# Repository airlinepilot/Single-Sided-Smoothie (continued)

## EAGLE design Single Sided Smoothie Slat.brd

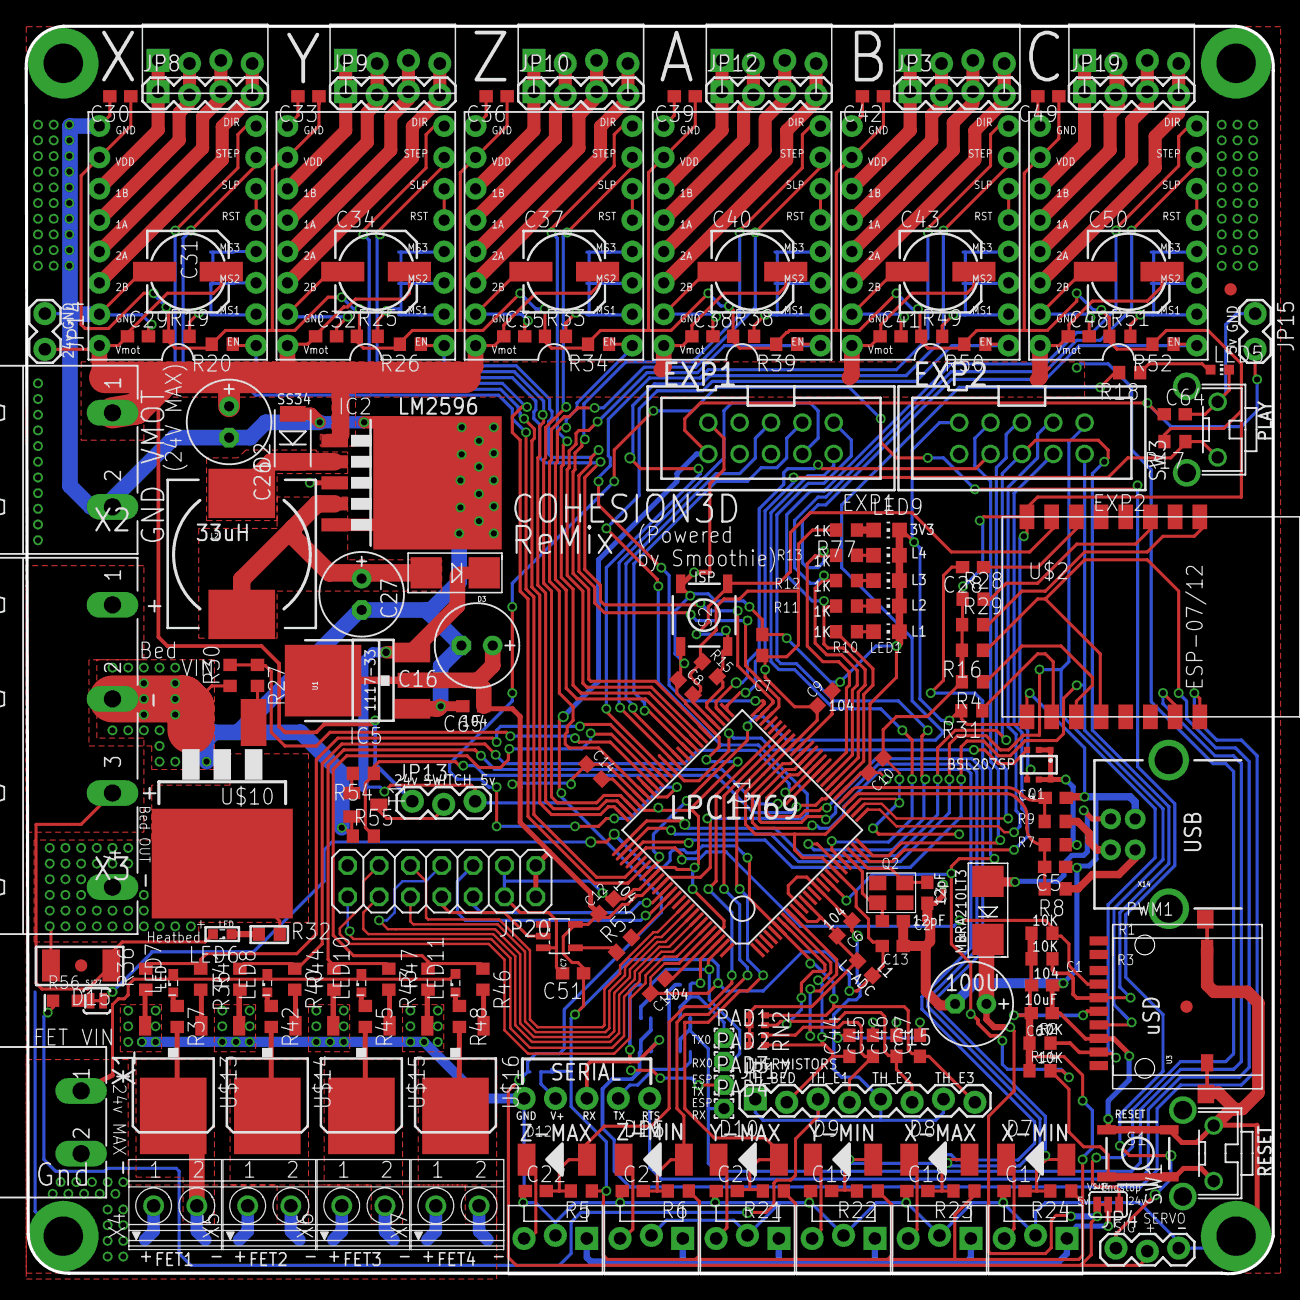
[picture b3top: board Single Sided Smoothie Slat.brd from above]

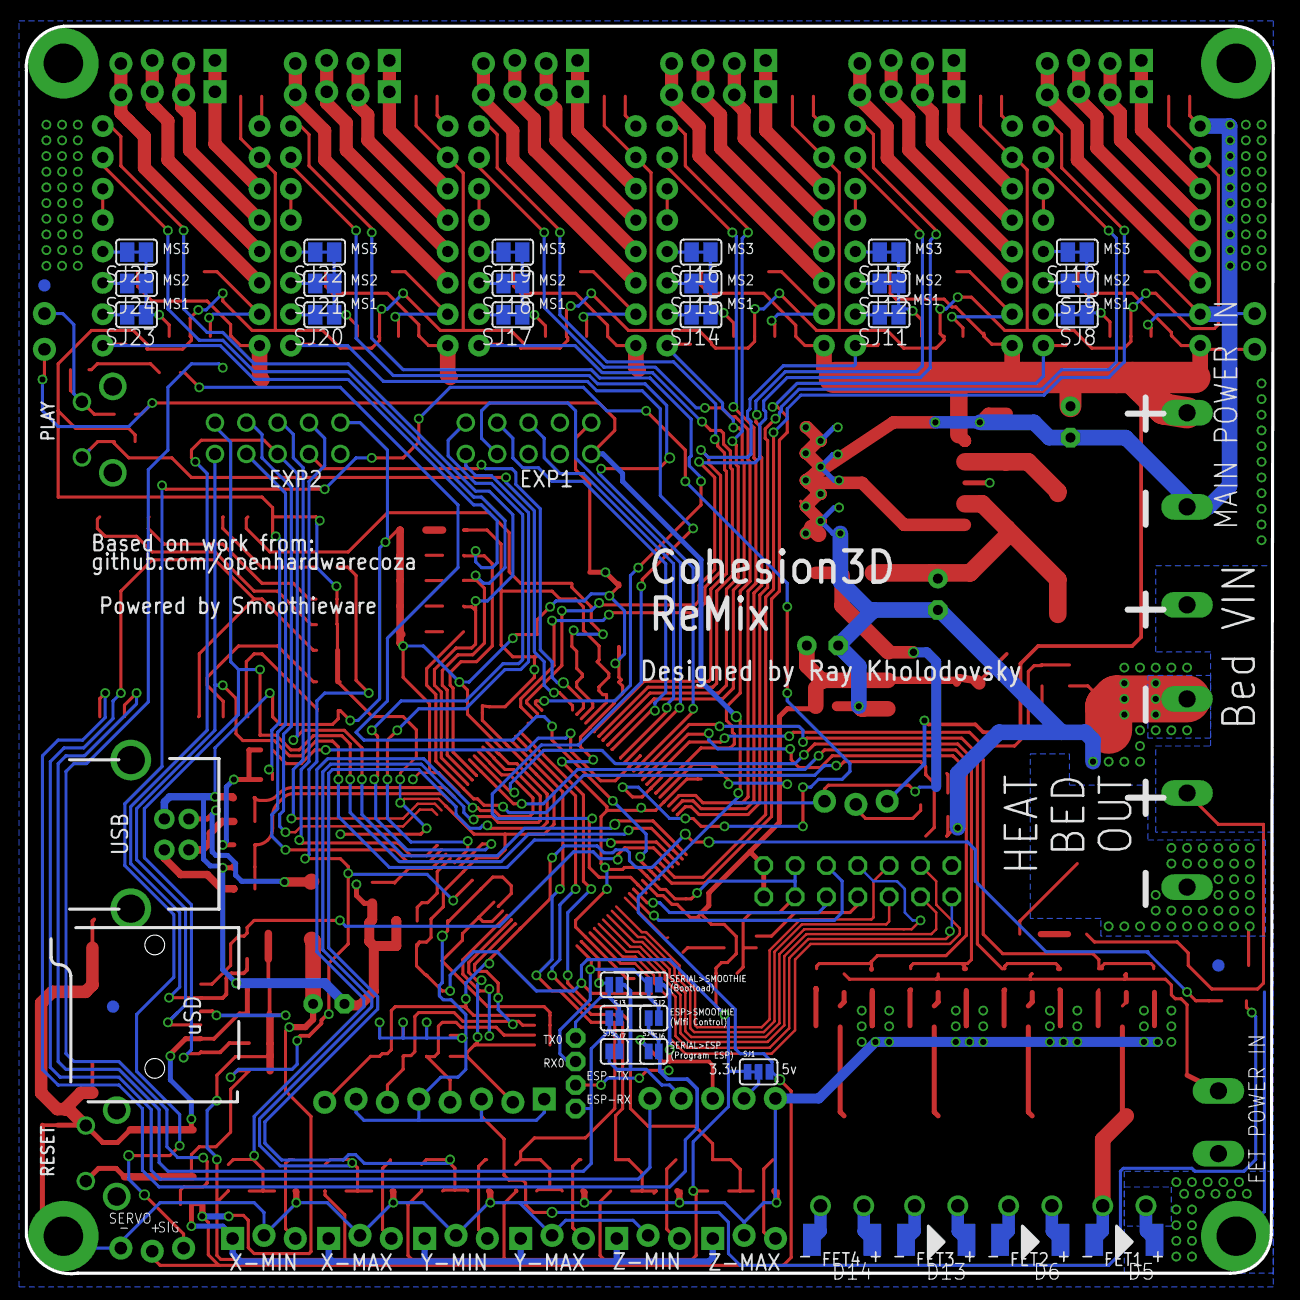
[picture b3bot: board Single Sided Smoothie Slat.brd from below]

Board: 2 copper layers, 101.0 x 101.0 mm, 233 parts (32 on the bottom side), 179 nets.

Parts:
C1, C6, C11, C12, C51, C65: .1uF; C0603
C2, C3: 12pF; C0603
C4, C5: 18pF; C0603
C7, C44, C45, C46, C47, C64, C67: 10uF; C0603
C8, C9, C10, C13, C14, C17, C18, C19, C20, C21, C22, C28, C29, C30, C32, C33, C35, C36, C38, C39, C41, C42, C48, C49: 104; C0603
C15: E2,5-7
C16: 100U; E2,5-7
C26, C27: 220u; E2,5-7
C31, C34, C37, C40, C43, C50: 100uF; 153CLV-0605
D1, D3: MBRA210LT3; SMADIODE
D2: DO-214AC
D5, D6, D7, D8, D9, D10, D11, D12, D13, D14, D15: M4; SOD87
EXP1, EXP2: 2510-; PAK100/2500-10
IC1: LPC1769; LQFP100
IC2: TO263-5
IC5: LD117ADT33TR; DPACK
IC7: 74LVC1G04; SOT23-5
JP1, JP2, JP6, JP7, JP11, JP18: MOLEX-1X4_LOCK
JP3, JP8, JP9, JP10, JP12, JP19: 1X04_LOCK
JP4, JP13: 1X03_LOCK
JP5: 1X05_NO_SILK
JP14, JP15: 1X02_LOCK
JP17: 1X08_LOCK
JP20: 2X07
L1: 0603
L2: 33uH; CDRH125
LED1, LED2, LED3, LED4, LED9: CHIP-LED0805
LED5: CHIP-LED0603
LED6, LED7: SML0603
LED8, LED10, LED11: LED; SML0603
PAD1, PAD2, PAD3, PAD4: 1,6/0,9
Q1: BSL207SP; SC74_INFINEON
Q2: 12MHz; CRYSTAL_3.2X2.5
R1, R2, R3, R4, R14, R15, R16, R17, R28, R29, R31: 10K; R0603
R5, R6, R20, R21, R22, R23, R24, R26, R34, R39, R50, R52: 10k; R0603
R7: 1.5K; R0603
R8, R9: 33R; R0603
R10, R11, R12, R13, R77: R0603
R18, R19, R25, R33, R38, R49, R51: 1k; R0603
R27, R35, R40, R43, R46, R54: 10r; R0603
R30, R36, R41, R44, R47, R55: 100k; R0603
R32, R37, R42, R45, R48: 1.5k; R0603
R53: 22R; R0603
R56: THERM; CT/CN0603
RN2: 4k7; 0603-ARV
S1, S2: TACTILE_SWITCH_SMD
SJ1, SJ26: SJ_3
SJ2, SJ3, SJ4, SJ5, SJ6, SJ7: SJ_2S
SJ8, SJ9, SJ10, SJ11, SJ12, SJ13, SJ14, SJ15, SJ16, SJ17, SJ18, SJ19, SJ20, SJ21, SJ22, SJ23, SJ24, SJ25: SJ
SJ27: THERM-JUMPER; SJ_2S-TRACE
SW1, SW3: SW_TACT_4P_B; SW_TACT_STANDARD_RIGHT_ANGLE
T1: BC817; SOT23-BEC
U1: SOT223
U3: USD-SOCKETUSD; USD-SOCKET-PP
U$1, U$5, U$6, U$7, U$8, U$9: POLOLU_A4983CARRIER; A4988BREAKOUT
U$2: ESP8266_ESP-12; ESP8266-ESP12
U$10: SUM120N04-1M7L-GE3; D2PACK
U$11, U$12, U$17, U$18, U$19, U$20: FIDUCIAL; FIDUCIAL_1MM
U$13, U$14, U$15, U$16: IRLR024; D-PAK_TO252AA
X1: MSTBA2
X2: GMSTBA2
X3: GMSTBA4
X4, X5, X6, X7: 1751248
X14: USBPTH; USB-B-PTH
XMN: MOLEX-1X3_LOCK
XMX: MOLEX-1X3_LOCK
YMN: MOLEX-1X3_LOCK
YMX: MOLEX-1X3_LOCK
ZMN: MOLEX-1X3_LOCK
ZMX: MOLEX-1X3_LOCK

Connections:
1A1M: JP6.2, JP8.2, U$1.1A
1A2M: JP2.2, JP9.2, U$5.1A
1A3M: JP7.2, JP10.2, U$6.1A
1A$4M: JP11.2, JP12.2, U$7.1A
1A$5M: JP1.2, JP3.2, U$8.1A
1A$6M: JP18.2, JP19.2, U$9.1A
1B1M: JP6.1, JP8.1, U$1.1B
1B2M: JP2.1, JP9.1, U$5.1B
1B3M: JP7.1, JP10.1, U$6.1B
1B$4M: JP11.1, JP12.1, U$7.1B
1B$5M: JP1.1, JP3.1, U$8.1B
1B$6M: JP18.1, JP19.1, U$9.1B
2: R4.1, U$2.3
2A1M: JP6.3, JP8.3, U$1.2A
2A2M: JP2.3, JP9.3, U$5.2A
2A3M: JP7.3, JP10.3, U$6.2A
2A$4M: JP11.3, JP12.3, U$7.2A
2A$5M: JP1.3, JP3.3, U$8.2A
2A$6M: JP18.3, JP19.3, U$9.2A
2B1M: JP6.4, JP8.4, U$1.2B
2B2M: JP2.4, JP9.4, U$5.2B
2B3M: JP7.4, JP10.4, U$6.2B
2B$4M: JP11.4, JP12.4, U$7.2B
2B$5M: JP1.4, JP3.4, U$8.2B
2B$6M: JP18.4, JP19.4, U$9.2B
3.3V: C1.2, C7.1, C8.2, C9.2, C10.2, C11.2, C12.2, C13.2, C14.2, C16.+, C30.1, C33.1, C36.1, C39.1, C42.1, C49.1, C51.1, C65.1, C67.2, IC1.19, IC1.28, IC1.42, IC1.54, IC1.71, IC1.84, IC1.96, IC5.4, IC7.5, JP5.4, JP20.1, JP20.2, L1.2, Q1.4, R1.2, R2.2, R3.2, R4.2, R5.1, R6.1, R14.2, R15.2, R16.2, R17.2, R19.1, R20.2, R21.1, R22.1, R23.1, R24.1, R25.1, R26.2, R28.1, R29.1, R33.1, R34.2, R38.1, R39.2, R49.1, R50.2, R51.1, R52.2, R77.2, SJ1.1, SJ1.2, U1.2, U1.4, U3.4, U$1.VDD, U$2.16, U$5.VDD, U$6.VDD, U$7.VDD, U$8.VDD, U$9.VDD
5V: C15.+, C64.1, D1.C, D3.C, EXP1.10, IC5.3, JP4.2, JP13.3, JP15.2, SJ1.3, SJ26.1, U1.3
5VREG: C27.+, D3.A, IC2.4, L2.2
12: C28.1, U$2.14
15: R31.1, U$2.2
24V: C26.+, C29.1, C31.+, C32.1, C34.+, C35.1, C37.+, C38.1, C40.+, C41.1, C43.+, C48.1, C50.+, IC2.1, JP13.1, JP14.2, SJ26.3, U$1.VMOT, U$5.VMOT, U$6.VMOT, U$7.VMOT, U$8.VMOT, U$9.VMOT, X2.1
AGND: C6.2, C44.2, C45.2, C46.2, C47.2, IC1.11, IC1.15, JP17.1, JP17.3, JP17.5, JP17.7, R56.1
AVCC: C6.1, IC1.10, IC1.12, L1.1, RN2.5, RN2.6, RN2.7, RN2.8
BUZZER-RRD: EXP1.1, IC1.20
DIR1: IC1.80, U$1.DIR
DIR2: IC1.49, U$5.DIR
DIR3: IC1.58, U$6.DIR
DIR4: IC1.56, U$7.DIR
DIR5: IC1.50, U$8.DIR
E1-CONTROL: D5.2, R37.2, U$13.4, X4.2
E2-CONTROL: D6.2, R42.2, U$14.4, X5.2
E3-CONTROL: D13.2, R45.2, U$15.4, X6.2
E4-CONTROL: D14.2, R48.2, U$16.4, X7.2
EN1: IC1.81, R20.1, U$1.EN
EN2: IC1.48, R26.1, U$5.EN
EN3: IC1.59, R34.1, U$6.EN
EN4: IC1.57, R39.1, U$7.EN
EN5: IC1.85, R50.1, U$8.EN
ENET_CRS: IC1.92, JP20.7
ENET_MDC: IC1.87, JP20.5
ENET_MDIO: IC1.86, JP20.6
ENET_REF_CLK: IC1.88, R53.2
ENET_RXD0: IC1.91, JP20.10
ENET_RXD1: IC1.90, JP20.9
ENET_TXD0: IC1.95, JP20.11
ENET_TXD1: IC1.94, JP20.14
ENET_TX_EN: IC1.93, JP20.12
ESPRX: PAD4.1, SJ5.2, SJ7.2, U$2.7
ESPTX: PAD3.1, SJ4.2, SJ6.2, U$2.8
GND: C1.1, C2.2, C3.2, C4.1, C5.1, C7.2, C8.1, C9.1, C10.1, C11.1, C12.1, C13.1, C14.1, C15.-, C16.-, C17.1, C18.1, C19.1, C20.1, C21.1, C22.1, C26.-, C27.-, C29.2, C30.2, C31.-, C32.2, C33.2, C34.-, C35.2, C36.2, C37.-, C38.2, C39.2, C40.-, C41.2, C42.2, C43.-, C48.2, C49.2, C50.-, C51.2, C64.2, C65.2, C67.1, D2.2, EXP1.9, EXP2.9, IC1.31, IC1.41, IC1.55, IC1.72, IC1.83, IC1.97, IC2.3, IC2.5, IC2.6, IC5.1, IC7.3, JP4.3, JP5.5, JP14.1, JP15.1, JP20.3, JP20.4, LED1.C, LED2.C, LED3.C, LED4.C, LED5.C, LED9.C, R30.1, R31.2, R36.1, R41.1, R44.1, R47.1, R55.1, S1.3, S1.4, S2.3, S2.4, SW1.2, SW3.2, T1.E, U1.1, U3.6, U3.CDNC1, U3.CDNC2, U3.GND1, U3.GND2, U$1.GND, U$1.GND@0, U$2.1, U$5.GND, U$5.GND@0, U$6.GND, U$6.GND@0, U$7.GND, U$7.GND@0, U$8.GND, U$8.GND@0, U$9.GND, U$9.GND@0, U$10.3, U$13.3, U$14.3, U$15.3, U$16.3, X1.2, X2.2, X3.2, X14.GND, XMN.2, XMX.2, YMN.2, YMX.2, ZMN.2, ZMX.2
HEATBED-CONTROL: D15.2, R32.2, U$10.2, X3.4
HEATBEDVIN: D15.1, LED6.A, X3.1, X3.3
HEATERVIN: D5.1, D6.1, D13.1, D14.1, LED7.A, LED8.A, LED10.A, LED11.A, X1.1, X4.1, X5.1, X6.1, X7.1
ISP_BOOT: IC1.53, R15.1, S2.1, S2.2, U$2.15
LED1: IC1.32, R10.2, R54.1, R55.2
LED2: IC1.33, R11.2, U$9.DIR
LED3: IC1.34, R12.2, U$9.STEP
LED4: IC1.35, R13.2, R52.1, U$9.EN
MOSI1: EXP1.3, IC1.60
unnamed: C2.1, IC1.22, Q2.2
unnamed: C3.1, IC1.23, Q2.1
unnamed: LED5.A, R18.1
unnamed: D11.1, ZMN.3
unnamed: D10.1, YMX.3
unnamed: SJ8.2, U$1.MS1
unnamed: D9.1, YMN.3
unnamed: SJ9.2, U$1.MS2
unnamed: D2.1, IC2.2, L2.1
unnamed: SJ10.2, U$1.MS3
unnamed: D8.1, XMX.3
unnamed: U$5.RST, U$5.SLP
unnamed: D7.1, XMN.3
unnamed: R25.2, SJ11.1, SJ12.1, SJ13.1
unnamed: SJ11.2, U$5.MS1
unnamed: D12.1, ZMX.3
unnamed: SJ12.2, U$5.MS2
unnamed: R28.2, U$2.11
unnamed: SJ13.2, U$5.MS3
unnamed: R27.2, U$10.1
unnamed: LED6.C, R32.1
unnamed: U$6.RST, U$6.SLP
unnamed: R33.2, SJ14.1, SJ15.1, SJ16.1
unnamed: SJ14.2, U$6.MS1
unnamed: SJ15.2, U$6.MS2
unnamed: SJ16.2, U$6.MS3
unnamed: R35.2, U$13.1
unnamed: R19.2, SJ8.1, SJ9.1, SJ10.1
unnamed: LED7.C, R37.1
unnamed: U$7.RST, U$7.SLP
unnamed: R38.2, SJ17.1, SJ18.1, SJ19.1
unnamed: SJ17.2, U$7.MS1
unnamed: SJ18.2, U$7.MS2
unnamed: U$1.RST, U$1.SLP
unnamed: SJ19.2, U$7.MS3
unnamed: R40.2, U$14.1
unnamed: LED8.C, R42.1
unnamed: R43.2, U$15.1
unnamed: LED10.C, R45.1
unnamed: R46.2, U$16.1
unnamed: LED11.C, R48.1
unnamed: U$8.RST, U$8.SLP
unnamed: R49.2, SJ20.1, SJ21.1, SJ22.1
unnamed: SJ20.2, U$8.MS1
unnamed: SJ21.2, U$8.MS2
unnamed: SJ22.2, U$8.MS3
unnamed: U$9.RST, U$9.SLP
unnamed: R51.2, SJ23.1, SJ24.1, SJ25.1
unnamed: SJ23.2, U$9.MS1
unnamed: Q1.1, Q1.2, Q1.5, Q1.6, R7.2
unnamed: SJ24.2, U$9.MS2
unnamed: SJ25.2, U$9.MS3
unnamed: R54.2, T1.B
unnamed: JP13.2, T1.C
unnamed: R8.1, X14.D+
unnamed: R9.1, X14.D-
unnamed: IC7.2, JP20.8
unnamed: IC7.4, R53.1
unnamed: LED9.A, R77.1
unnamed: LED4.A, R13.1
unnamed: LED3.A, R12.1
unnamed: LED2.A, R11.1
unnamed: LED1.A, R10.1
P1_22-3RD-SMALL-FET: IC1.36, R43.1, R44.2
P1_23-3RD-LARGE-FET: IC1.37, R40.1, R41.2
P1_30_CLICK-ON-RRD: EXP1.2, IC1.21
P2.6_FAN_FET: IC1.67, R46.1, R47.2
P2.7_HOTEND_FET: IC1.66, R35.1, R36.2
P2.9: IC1.64, Q1.3
PLAY: IC1.51, R17.1, SW3.1
PLAY_LED: IC1.82, R18.2
PWM0_PSU_OUT: IC1.69, JP4.1
PWM1_BED_HEATER: IC1.68, R27.1, R30.2
RESET: C28.2, IC1.17, R14.1, S1.1, S1.2, SW1.1
RESET1: R29.2, U$2.9
RTS: JP5.1, R16.1, U$2.4
RX_0: IC1.99, PAD2.1, SJ2.2, SJ6.1
RX_FT: JP5.3, SJ2.1, SJ4.1
SCK1: EXP1.5, IC1.62
SD-CD-ON-RRD: EXP2.7, IC1.25
SD-CS-ON-RRD: EXP2.4, IC1.24
SD_CD/KILL-ON-RRD: EXP2.8, IC1.52
SD_CS: IC1.79, R1.1, U3.2
SD_IRQ-ENC-A-ON-RRD: EXP2.5, IC1.27
SD_MISO: EXP2.1, IC1.77, R2.1, U3.7
SD_MOSI: EXP2.6, IC1.76, R3.1, U3.3
SD_SCK: EXP2.2, IC1.78, U3.5
SD_WP-ENC-B-ON-RRD: EXP2.3, IC1.26
SSEL1: EXP1.4, IC1.63
STP1: IC1.75, U$1.STEP
STP2: IC1.74, U$5.STEP
STP3: IC1.73, U$6.STEP
STP4: IC1.70, U$7.STEP
STP5: IC1.65, U$8.STEP
TH1_HOTEND: C45.1, IC1.9, JP17.4, RN2.2
TH2_BED: C44.1, IC1.8, JP17.2, RN2.1
TH3: C46.1, IC1.7, JP17.6, RN2.3
TH4: C47.1, IC1.6, JP17.8, R56.2, RN2.4, SJ27.1, SJ27.2
TX_0: IC1.98, PAD1.1, SJ3.2, SJ7.1
TX_FT: JP5.2, SJ3.1, SJ5.1
USB_D+: C5.2, IC1.29, R7.1, R8.2
USB_D-: C4.2, IC1.30, R9.2
V-ENDSTOP: SJ26.2, XMN.1, XMX.1, YMN.1, YMX.1, ZMN.1, ZMX.1
VUSB: D1.A, X14.VBUS
X_MAX: C18.2, D8.2, IC1.39, R23.2
X_MIN: C17.2, D7.2, IC1.38, R24.2
Y_MAX: C20.2, D10.2, IC1.43, R21.2
Y_MIN: C19.2, D9.2, IC1.40, R22.2
Z_MAX: C22.2, D12.2, IC1.45, R5.2
Z_MIN: C21.2, D11.2, IC1.44, R6.2

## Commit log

2016-05-10 :neckbeard: Added .gitattributes & .gitignore files
2016-05-10 Inserted derived work
2016-08-30 Version 3 using Micro Brain Carrier Board, Motors routed using 20/20
2016-08-31 Motors consolidated, 4 mosfets placed, first glcd attempt
2016-08-31 Dedicated Power In for Bed MOSFET, rev1 board don
